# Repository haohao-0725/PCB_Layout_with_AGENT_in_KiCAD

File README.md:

# PCB Layout with an AI Agent in KiCad (`kicad-clean-pcb`)

[繁體中文說明](README.zh-TW.md)

**An AI agent takes your working prototype to a tidy, fab-ready KiCad board: you approve every
decision, the placement is checked on paper before routing, and tidiness is measured, not
eyeballed.**

See a complete board generated end to end with the bundled tools, from wiring plan to fab zip:
[examples/stepper-carrier-2axis](examples/stepper-carrier-2axis/) (NUCLEO-F446ZE + 2 × TMC2209,
4 layers, ERC/DRC/parity 0, no vias).

An **Agent Skill for Claude Code and OpenAI Codex**. It takes a **KiCad PCB** from a working
prototype to fab-ready **Gerber and drill files**, and keeps you in the loop:

- you choose the design style up front,
- you approve every add-on circuit in a yes/no checklist,
- you confirm the placement on a **1:1 printout before a single track is routed**.

It is **not an autorouter**. It is the workflow, layout rules and checks that make an AI agent
behave like a careful PCB designer, for hand-soldered control boards, motor-driver boards and
module carrier boards.

## Why this exists

It came out of turning a perfboard prototype into a 4-layer carrier board. The prototype had an
MCU dev board, stepper-driver modules, encoder receivers and current-sense modules.

The agent's first attempt used automatic placement and grid routing. It passed DRC, but it had:

- about 10,000 zigzag track segments,
- four copper pours,
- a layout nobody could follow.

The restructured board had about 600 segments and 30 vias, one GND plane, and a third less
board area.

The 1:1 paper check came too late, after routing. It found a USB port blocked by a header row,
a fuse holder whose pitch didn't match the real part, and a terminal block that duplicated one
already on a module. All three meant rerouting.

This skill captures what fixed those problems, so the next board doesn't repeat them:

- **Decide in writing, early.** Preferences and add-on circuits are settled before the
  schematic, in a file both sides can read (`PCB_DECISIONS.md`).
- **Place, print, confirm, then route.** Mechanical mistakes surface on paper, not after
  routing.
- **Route by function group, one group at a time.** Straight lines and 45° corners, a main
  direction per layer, few vias. Run DRC after each group.
- **Nothing unrequested.** No protection, buffers or test points the user didn't approve. And
  no silently skipped protection either.

## What's inside

- **A 7-stage workflow with 4 checkpoints:** requirements and wiring → parts and decisions →
  schematic → placement (1:1 check) → routing → verification and fab files → close-out.
- **Three design presets, plus 17 adjustable axes:** Tidy & readable, Compact / shortest,
  Robust / max electrical. The axes cover stackup, vias, pours, protection policy, current
  target, temperature-rise limit, assembly method, silkscreen, checkpoint cadence and more.
- **`PCB_DECISIONS.md`, a yes/no handshake template.** It has:
  - a scope check (mains, >60 V, Li-ion, high-speed, safety-critical),
  - your preferences,
  - one row per optional protection or add-on circuit,
  - one row per optional technical check,
  - checkpoint sign-offs and a change log.

  A blank row means "not approved".
- **Reference guides:** layout rules per style; circuit policy (add-on classes A–D, current
  ratings, reverse-polarity options, regenerated motor energy); a routing playbook with
  stackup options; verification and order-spec templates; KiCad 10 scripting notes.
- **Board tools (`kcp`)** that read the `.kicad_pcb` file directly, plus four scripts. Both are
  listed under [Tools and scripts](#tools-and-scripts). The tidiness lint turns "is this layout
  readable?" into numbers: segments per mm, zigzag turns, off-angle segments, vias on power
  nets, layer directions, non-GND pours, part-row alignment.

## Is it for you?

**Good fit**

- You have a working prototype (perfboard, breadboard, jumper wires, dev boards and modules) and
  want a real PCB.
- Low and medium-speed boards: microcontroller I/O, motor drivers, sensors, encoders,
  RS-422/RS-485, I²C/SPI/UART.
- You use Claude Code, Codex or another agent that supports Agent Skills, and you want to
  approve the important decisions yourself.

**Not a fit**

- RF, DDR, USB high-speed or other controlled-impedance designs; mains-powered or isolated
  supplies; battery charging; anything above 60 V DC; safety-critical or medical devices. The
  skill's scope check stops and says so.
- "Generate my whole board without asking me anything." This skill asks, on purpose, at four
  checkpoints.

## Requirements and version notes

| | Tested | Notes |
|---|---|---|
| KiCad | **10.0.x** | `kicad-cli` options and Gerber file naming change between versions. The skill checks `--help` and reads Gerber layers from X2 attributes instead of file extensions |
| OS | Windows 10 | macOS and Linux should work, but the paths in the docs are Windows-first and untested elsewhere |
| Python for `kcp` and the board scripts | 3.9+ (stdlib only) | Reads and writes the KiCad files directly; nothing imports `pcbnew` (deprecated, removed in KiCad 11). `kicad-cli` is used for DRC, ERC, netlists, previews and fab output |
| Python for Gerber tools | 3.8+ (stdlib only) | `gerber_readback.py` and `compare_gerbers.py` need no KiCad |
| Agents | Claude Code, Codex | Any agent that reads `SKILL.md` folders (the Agent Skills format) should work |

## Install

**Pick one method.** If you copied the skill folder into `~/.claude/skills/` before and now
install the plugin, delete `~/.claude/skills/kicad-clean-pcb` first: with both installed, the
name `kicad-clean-pcb` resolves to the copied folder and the agent may follow that older copy.
Start a new session after installing or updating, because skills and MCP tools load when a
session starts. To check, ask the agent to run `python <skill>/kcp doctor --markdown` (MCP tool
`check_setup`): it lists every copy of the skill on the machine with its version and says what
to update or remove.

### Claude Code: plugin marketplace (recommended)

In a Claude Code session:

```text
/plugin marketplace add haohao-0725/PCB_Layout_with_AGENT_in_KiCAD
/plugin install kicad-clean-pcb@pcb-layout-with-agent
```

### Claude Code: copy the skill folder

```bash
git clone https://github.com/haohao-0725/PCB_Layout_with_AGENT_in_KiCAD.git
cp -r PCB_Layout_with_AGENT_in_KiCAD/skills/kicad-clean-pcb ~/.claude/skills/
```

For a single project, use `<project>/.claude/skills/` instead.

### Codex

```bash
cp -r PCB_Layout_with_AGENT_in_KiCAD/skills/kicad-clean-pcb ~/.agents/skills/
```

For a single repository, use `<repo>/.agents/skills/`. Older Codex releases read
`~/.codex/skills/`. Restart Codex after installing.

### Updating

Claude Code doesn't update plugins from third-party marketplaces on its own (auto-update is off
for them by default), and a session keeps the version it started with. To update:

```bash
claude plugin marketplace update pcb-layout-with-agent
claude plugin update kicad-clean-pcb@pcb-layout-with-agent
```

Or, in a session: `/plugin`, **Installed** tab, `kicad-clean-pcb`, **Update now**. To have it
update by itself: `/plugin`, **Marketplaces** tab, `pcb-layout-with-agent`, **Enable
auto-update**. Then start a new session. To update a copied folder, `git pull` the clone and copy
the folder again. `kcp doctor` reports any copy that is older than the newest one on the machine.

**Claude desktop app.** The app runs its own copy of Claude Code, which is not on PATH, so a
terminal answers that it can't find `claude`. Ask the agent in a Code session to update the
plugin: `kcp doctor` gives it the full path of the app's copy. Or, on Windows, run it yourself in
PowerShell (the folder name has the app's version in it and changes when the app updates):

```powershell
$claude = (Get-ChildItem "$env:APPDATA\Claude\claude-code\*\*\claude.exe" | Sort-Object LastWriteTime | Select-Object -Last 1).FullName
& $claude plugin marketplace update pcb-layout-with-agent
& $claude plugin update kicad-clean-pcb@pcb-layout-with-agent
```

Then start a new session.

### Windows (PowerShell)

```powershell
Copy-Item -Recurse PCB_Layout_with_AGENT_in_KiCAD\skills\kicad-clean-pcb $HOME\.claude\skills\
```

## Quick start

Just describe the board. For example:

- "Turn my perfboard stepper controller into a PCB. Here are the pin map, BOM and photos."
- "Here's my KiCad schematic. Help me place it and route it so it's readable."
- "Check these Gerbers before I order them."

The agent starts with the scope check and asks you to pick a preset. Then it creates
`PCB_DECISIONS.md` in your project. From there, every checkpoint is a single message listing
everything that needs your answer.

## Design presets

| | T · Tidy & readable | C · Compact / shortest | R · Robust / max electrical |
|---|---|---|---|
| Goal | Read the layout at a glance; easy to hand-solder and modify | Smallest board, shortest connections, lowest cost | Best signal integrity, thermal margin and fault tolerance |
| Routing | Straight + 45°, one direction per layer, ordered lanes | Shortest 45° paths | As T, plus return-path rules |
| 4-layer stackup | Sig / GND / GND / Sig | Sig / GND / Power / Sig | Sig / GND / GND / Sig |
| Add-on circuits | Minimal (prototype is the baseline) | Minimal | Full protection at external interfaces |
| Current target / ΔT limit | 2 × measured / 20 °C | 2 × measured / 20 °C | Worst case / 10 °C |

You can mix and match, e.g. a tidy layout with full protection. All presets keep the 1:1 fit
check, measured footprints, native checks at zero, and a Gerber readback with a layer-order
table.

## The workflow

| Stage | Output | You confirm |
|---|---|---|
| 0. Scope, profile, preferences | `PCB_DECISIONS.md` Part A | ✔ |
| 1. Hardware list, requirements, wiring plan | Project brief | ✔ |
| 2. Parts gaps, add-on decisions | BOM, measured dimensions, yes/no rows answered | ✔ |
| 3. Schematic | ERC clean, netlist checked against the wiring plan | if needed |
| 4. Placement | Previews and a **1:1 fit-check PDF** | ✔ **no routing before this** |
| 5. Routing | Grouped routing, DRC after each group | at the end |
| 6. Verification and fab files | DRC/parity zero, Gerbers + drill + readback, order spec | ✔ |
| 7. Close-out | One rebuild entry point, archived old files, handoff notes | — |

## Tools and scripts

### Board tools: `kcp`

Any Python 3.9+, no KiCad needed except for `drc` and `erc`. Each command prints JSON, or
Markdown tables with `--markdown`. Exit code 1 means the check failed; 2 means the tool could
not run.

| Command | What it does |
|---|---|
| `inspect` | The board as JSON: outline size, layers and stackup, footprints with position, rotation, side, courtyard and pads, nets with netclass and routing stats, tracks, vias and zones. `--drc` adds unconnected items per net |
| `lint` | Tidiness score against a preset (T, C or R), pass / warn / fail per metric. Thresholds live in `kcp/presets/lint.json`; pass your own copy with `--thresholds`. Give it a layer plan (`examples/layer-plans/`) to check each layer's main direction |
| `decisions` | Blank rows in `PCB_DECISIONS.md`, in any language. `--checkpoint CP2` exits 1 while anything CP2 needs is unanswered |
| `drc`, `erc` | kicad-cli DRC / ERC summarised by type, unconnected items per net. DRC also lists every item with the parts involved and its position, named the same in any KiCad UI language. It runs on a temporary copy, so nothing is written next to your board; `--refill --save` has KiCad fill the zones and save the board |
| `place` | `fit-check` (courtyard overlaps, edge distance, silkscreen past the edge, keep-outs), `move`, `row`, `edge` (courtyard and silkscreen flush with the edge; `--entry auto` turns screw terminals, JST PH/XH/EH, barrel jacks and USB parts so the cable goes in from outside). Writes refuse while KiCad has the project open |
| `route` | `path`: pad → bend points → pad, written only if every segment is 0/45/90° and keeps the netclass clearance; otherwise a list of conflicts. `lane`: crossing-free order for a lane. `cleanup`: merge collinear segments |
| `previews`, `tracedrop` | Review PDFs/PNGs (top layer drawn last; a page per outer layer when it has a pour) and the 1:1 fit-check page; voltage drop and temperature rise of a net |
| `fab` | Gerbers + drill, a zip with README.txt and SHA256SUMS.txt, and a readback of the zip against the board (size, copper layers, PTH, NPTH) |
| `new` | Starts a generator project: build, place, route and rebuild scripts for a placeholder board that passes every check, ready to replace with your wiring plan |
| `doctor` | Which copies of the skill are installed (plugin, copied folders) with their versions, which one runs, and what to update |

```bash
python skills/kicad-clean-pcb/kcp inspect board.kicad_pcb --summary --markdown
python skills/kicad-clean-pcb/kcp lint board.kicad_pcb --preset T --layer-plan examples/layer-plans/4L-S1.json --markdown
python skills/kicad-clean-pcb/kcp decisions PCB_DECISIONS.md --checkpoint CP2
python skills/kicad-clean-pcb/kcp drc board.kicad_pcb --refill
python skills/kicad-clean-pcb/kcp fab board.kicad_pcb --out-dir fab --readme order_spec.txt
python skills/kicad-clean-pcb/kcp new my_board --copper 2 && python my_board/rebuild_my_board.py
```

On the board this skill came from, the lint separates the two versions clearly:

| Metric | Autorouted draft | Restructured board |
|---|---:|---:|
| Segments per mm of track | 1.00 | 0.09 |
| Turns per 10 mm (zigzag) | 8.8 | 0.5 |
| Segments not at 0/45/90° | 79 | 0 |
| Vias on power / phase nets | 24 | 0 |
| Pours on nets other than GND | 3 | 0 |
| Worst resistor-row misalignment | 1.35 mm | 0 mm |
| Result (preset T) | fail on 11 metrics | warn (11 short S-bends to review) |

### Scripts

| Script | What it does | Run with |
|---|---|---|
| `export_previews.py` | Routing, assembly and inner-plane previews (PDF + PNG) and a 1:1 fit-check PDF on A4/A3 (same as `kcp previews`) | Python 3.9+ |
| `trace_drop.py` | Voltage drop and IPC-2221 temperature rise along a net's tracks, to each load (same as `kcp tracedrop`) | Python 3.9+ |
| `gerber_readback.py` | Layer functions and copper order from X2 attributes, board outline size, PTH/NPTH hole and slot counts, with optional expected values | Python 3.8+ |
| `compare_gerbers.py` | Geometry diff of two Gerber/drill bundles: lines, arcs, flashes, regions, holes and slots | Python 3.8+ |

```bash
# Windows example; on Windows set PYTHONUTF8=1
python skills/kicad-clean-pcb/scripts/trace_drop.py board.kicad_pcb --net +5V --source J1.1 --load U3.8=0.15 --load J5.1=0.2
python skills/kicad-clean-pcb/scripts/gerber_readback.py fab.zip --expect-size 100x80 --expect-copper 4 --markdown
python skills/kicad-clean-pcb/scripts/compare_gerbers.py old.zip new.zip
```

Run the unit tests (no KiCad needed; one integration test runs only when `kicad-cli` is installed):

```bash
python -m unittest discover -s tests -v
```

## MCP server and live mode

The same tools are available as an MCP server, one tool per `kcp` command (18 tools: setup check,
inspect, lint, decisions, DRC, ERC, place, route, previews, trace drop, fab output, Gerber readback
and compare; the table is in `SKILL.md`). Every result carries `kcp_version`, the version of the
server that answered. Read-only tools are marked as such; tools that write say so.
The MCP tools check, place and route a board and write the fab files. Creating a schematic and a
board from nothing needs an agent that can run Python (`kcp new`).

- **Claude Code:** installing the plugin registers the server (`mcpServers` in `.claude-plugin/plugin.json`
  runs `python <plugin>/skills/kicad-clean-pcb/kcp mcp`). It needs `python` on your PATH (3.9+);
  where only `python3` exists (common on macOS and Linux), make `python` available first (for
  example `python-is-python3` on Debian/Ubuntu), or the server does not start.
- **Codex** (`~/.codex/config.toml`):

  ```toml
  [mcp_servers.kicad-clean-pcb]
  command = "python"
  args = ["/path/to/skills/kicad-clean-pcb/kcp", "mcp"]
  ```
- **Other agents:** any MCP client that starts a stdio server:
  `{"command": "python", "args": ["/path/to/skills/kicad-clean-pcb/kcp", "mcp"]}`.

With the official SDK installed (`pip install mcp`, 1.x or 2.x) the server uses it; without it, a
small built-in stdio server with the same tools runs instead, so nothing extra is required.

**Live mode (KiCad IPC API).** Pass `live` instead of a board file to `inspect`, `lint`,
`place fit-check`, `place move` and `route path` (CLI or MCP) to work on the board open in KiCad,
saved or not. Every edit is one KiCad commit named like `kcp: route X_DIR`, so one Ctrl+Z undoes
it, and nothing is written when a check fails. To use it:

1. `pip install kicad-python` (module `kipy`; 0.8 targets KiCad 10.0.6, so update KiCad first).
2. In KiCad, enable the API server: Preferences → Plugins (KiCad 9/10). It is stored as
   `api.enable_server` in `kicad_common.json`.
3. Keep KiCad running with the board open.

KiCad 10's API has no schematic commands and cannot load library footprints, so schematic work,
new footprints and fab output stay on the file backend and `kicad-cli`. Live mode is covered by
tests against a stand-in for `kipy`; it has not yet been run against a live KiCad session in this
repository.

## Saving your defaults

If you always start the same way, keep a filled Part A in a file of your own, **outside** the
installed skill folder (updates overwrite it). Start from
[`examples/defaults/PCB_PART_A_DEFAULTS.md`](examples/defaults/PCB_PART_A_DEFAULTS.md), then
point your agent at it from your global notes (`~/.claude/CLAUDE.md` for Claude Code, `AGENTS.md`
for Codex):

```markdown
## PCB work
For the kicad-clean-pcb skill, my default Part A is in ~/pcb-defaults/PCB_PART_A_DEFAULTS.md.
Copy it into each new PCB_DECISIONS.md and ask me once to confirm it.
```

At stage 0 the agent copies it into the project and asks for one confirmation instead of going
through every axis.

## Repository layout

```text
.claude-plugin/          plugin.json (also registers the kcp MCP server) + marketplace.json
skills/kicad-clean-pcb/
  SKILL.md               workflow, checkpoints, principles
  references/            preferences, layout rules, circuit policy, routing, checks, KiCad scripting, regional ordering
  assets/                PCB_DECISIONS and PROJECT_BRIEF templates
  kcp/                   board tools: inspect, lint, decisions, drc/erc, place, route, previews,
                         tracedrop, MCP server, live IPC backend (Python package, stdlib only)
  scripts/               preview, trace, readback and compare tools
  agents/openai.yaml     Codex UI metadata
examples/                saved-defaults example, layer plans for `kcp lint`
tests/                   unit tests and a hand-written test board
docs/                    README images, release steps (RELEASING.md)
pyproject.toml           packaging for `pip install` (optional; the skill folder works on its own)
```

## Limitations and disclaimer

- **Rules of thumb, not a standard.** The rules come from hand-built, low-to-medium-speed boards.
  Verify critical numbers (current, temperature, clearance) against datasheets, IPC standards
  and your fab's capabilities.
- **CAD-clean is not hardware-verified.** Passing DRC says nothing about waveforms, temperature
  or real-world plugging. Test the real board.
- **Estimates only.** `trace_drop.py` uses the IPC-2221 formula and ignores pours, pads and
  connectors.
- **What the Gerber tools skip.** They don't evaluate aperture-macro bodies or step-and-repeat
  blocks.
- **The agent never orders or pays.** It prepares files and specs; you place the order.
- **No warranty.** Provided as is under the MIT license. You are responsible for the boards you
  build.

## Contributing

Issues and pull requests are welcome. These help most:

- reports from other KiCad versions and operating systems,
- layout rules for board types not covered here,
- regional ordering notes,
- a port of the board scripts to KiCad's IPC API.

Please keep proposed rules generic. No project-specific numbers.

## License

[MIT](LICENSE)

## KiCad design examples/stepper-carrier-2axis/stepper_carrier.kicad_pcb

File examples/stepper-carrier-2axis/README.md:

# 範例：2 軸步進馬達載板（NUCLEO-F446ZE ＋ 2 × TMC2209）

`kicad-clean-pcb` skill 從頭走完 Stage 0–6 的完整範例：接線規劃 → 原理圖 → 擺放 → 走線 → 檢查 → 製造檔。
所有 KiCad 檔都由腳本產生，**全程沒有用到 pcbnew（SWIG）**，只用 skill 內的 `kcp` 工具和 `kicad-cli`。

## 狀態

| 項目 | 結果 | 類型 |
|---|---|---|
| ERC | 0 錯誤、0 警告 | CAD 已檢查 |
| KiCad netlist 對照接線規劃 | 24 個元件、每支腳都一致 | CAD 已檢查 |
| DRC／未連線／schematic parity | 0／0／0 | CAD 已檢查 |
| via | 0 個（換層都在 THT 焊盤上） | CAD 已檢查 |
| 鋪銅 | 只有 In1.Cu、In2.Cu 兩層 GND | CAD 已檢查 |
| 整齊度 lint（預設 T、4L-S1 layer plan） | 全部 pass：每 mm 0.10 段、每 10 mm 0.41 個轉折、0 條斜角線段 | CAD 已檢查 |
| 壓降／溫升 | VM 最遠 64 mV、+5V 33 mV、最熱一段 ΔT 4.7 °C | 估算（IPC-2221，只算走線） |
| 製造檔回讀 | 126 × 146 mm、4 層、222 PTH、4 NPTH，與板子一致 | CAD 已檢查 |
| 1:1 實物比對（CP4） | 位置都正確（使用者，2026-10-30） | 實物比對 |
| LM2596 模組焊盤位置 | 1:1 列印比對位置正確；封裝尺寸原本是典型值 | 實物比對 |
| 下單 | 不下單：這塊板只用來示範工具 | — |

整齊度報告：[reports/lint.md](reports/lint.md)。決策紀錄：[PCB_DECISIONS.md](PCB_DECISIONS.md)。
專案簡報：[PROJECT_BRIEF.md](PROJECT_BRIEF.md)。下單規格：[ORDER_SPEC.md](ORDER_SPEC.md)。
實板驗收與量測紀錄（下單、組裝後填寫）：[BRINGUP.md](BRINGUP.md)。

## 板子內容

- **電源：** 12–24 V 端子 J1 → 3 A 慢熔 F1 → 串聯蕭特基 D1（反接保護）→ VM。
  VM 經 B.Cu 1.5 mm 主幹送到兩顆驅動器（各有 470 µF ＋ 100 nF）與 LM2596 降壓模組。
- **5 V：** LM2596 模組輸出接 Nucleo 的 E5V（CN11-6）。
- **驅動器：** 兩顆 MKS TMC2209 V2.0，獨立模式（MS1＝MS2＝GND 為 1/8 微步，PDN_UART 接 GND），
  EN 有 10 kΩ 上拉，MCU 拉低才致能。VIO 接 Nucleo 的 3.3 V。
- **限位：** 兩路常開開關輸入：1 kΩ 串聯 ＋ 10 nF ＋ 10 kΩ 上拉到 3.3 V。
- **版面：** 驅動器與電源在左、Nucleo 在右；所有電線從左緣進板；兩個軸用同一套模板。

## 檔案

| 檔案 | 用途 | 改什麼要改這裡 |
|---|---|---|
| `build_stepper_carrier.py` | 接線規劃（零件、每支腳的 net）、自建封裝（實測尺寸）、netclass 與設計規則 | 電路、元件值、封裝、線寬 |
| `place_stepper_carrier.py` | 板框、GND 平面、每個零件的位置、禁區、絲印 | 位置、方向、板子尺寸 |
| `route_stepper_carrier.py` | 每群一個函式：power、phases、mcu、limits | 走線 |
| `rebuild_stepper_carrier.py` | 唯一入口，從規劃一路做到製造包 | — |
| `stepper_carrier.kicad_*`、`*.kicad_sym`、`*.pretty`、`bom.csv`、`design.json` | 產生物，**不要在 KiCad 直接改** | 改上面的腳本後重建 |
| `reports/` | ERC、netlist 比對、fit check、DRC、lint、壓降、回讀 | — |
| `review/` | 走線、裝件、內層預覽（PNG＋PDF），1:1 試合 PDF | — |
| `fab/` | Gerber、鑽孔與製造壓縮包（含 README.txt 與 SHA256SUMS.txt） | — |

## 重建

先關閉 KiCad（資料夾裡有 `~*.lck` 時腳本會拒絕執行），再用任何 Python 3.9 以上執行：

```bash
python examples/stepper-carrier-2axis/rebuild_stepper_carrier.py
```

需要 KiCad 10 的 `kicad-cli`；要輸出 PNG 預覽還需要 Poppler 的 `pdftoppm`。每一步印一行 `[OK]`／`[FAIL]`，
失敗就停。完整重建約 15 秒。

## 組裝與上電

1. 先焊矮的零件（電阻、陶瓷電容、二極體），再焊排母、端子台、保險絲座、電解電容。
   D1 直立，陰極（色環）在焊盤 1（方形，VM 那側）。
2. **還沒插 Nucleo 和驅動器之前**：接上 12–24 V，把 LM2596 模組調到 5.0 V。
3. 斷電，把 Nucleo 的電源跳線設在 E5V（見 UM1974），插上 Nucleo。
   **不要把載板的 +5V 接到 CN11-18（Nucleo 的 5 V 輸出）。**
4. 斷電，依絲印方向插上驅動器（EN／VM 那一端朝下），先把 VREF 旋鈕調低。
5. 上電後才連 ST-LINK USB。插拔模組一律先斷電。

## 這個範例刻意沒做的事

- 沒有 TVS、ESD、測試點、電源 LED（精簡策略，見 PCB_DECISIONS Part B）。
- 沒有下單。下單前要先做 CP4 的 1:1 實物比對，並量好 LM2596 模組。

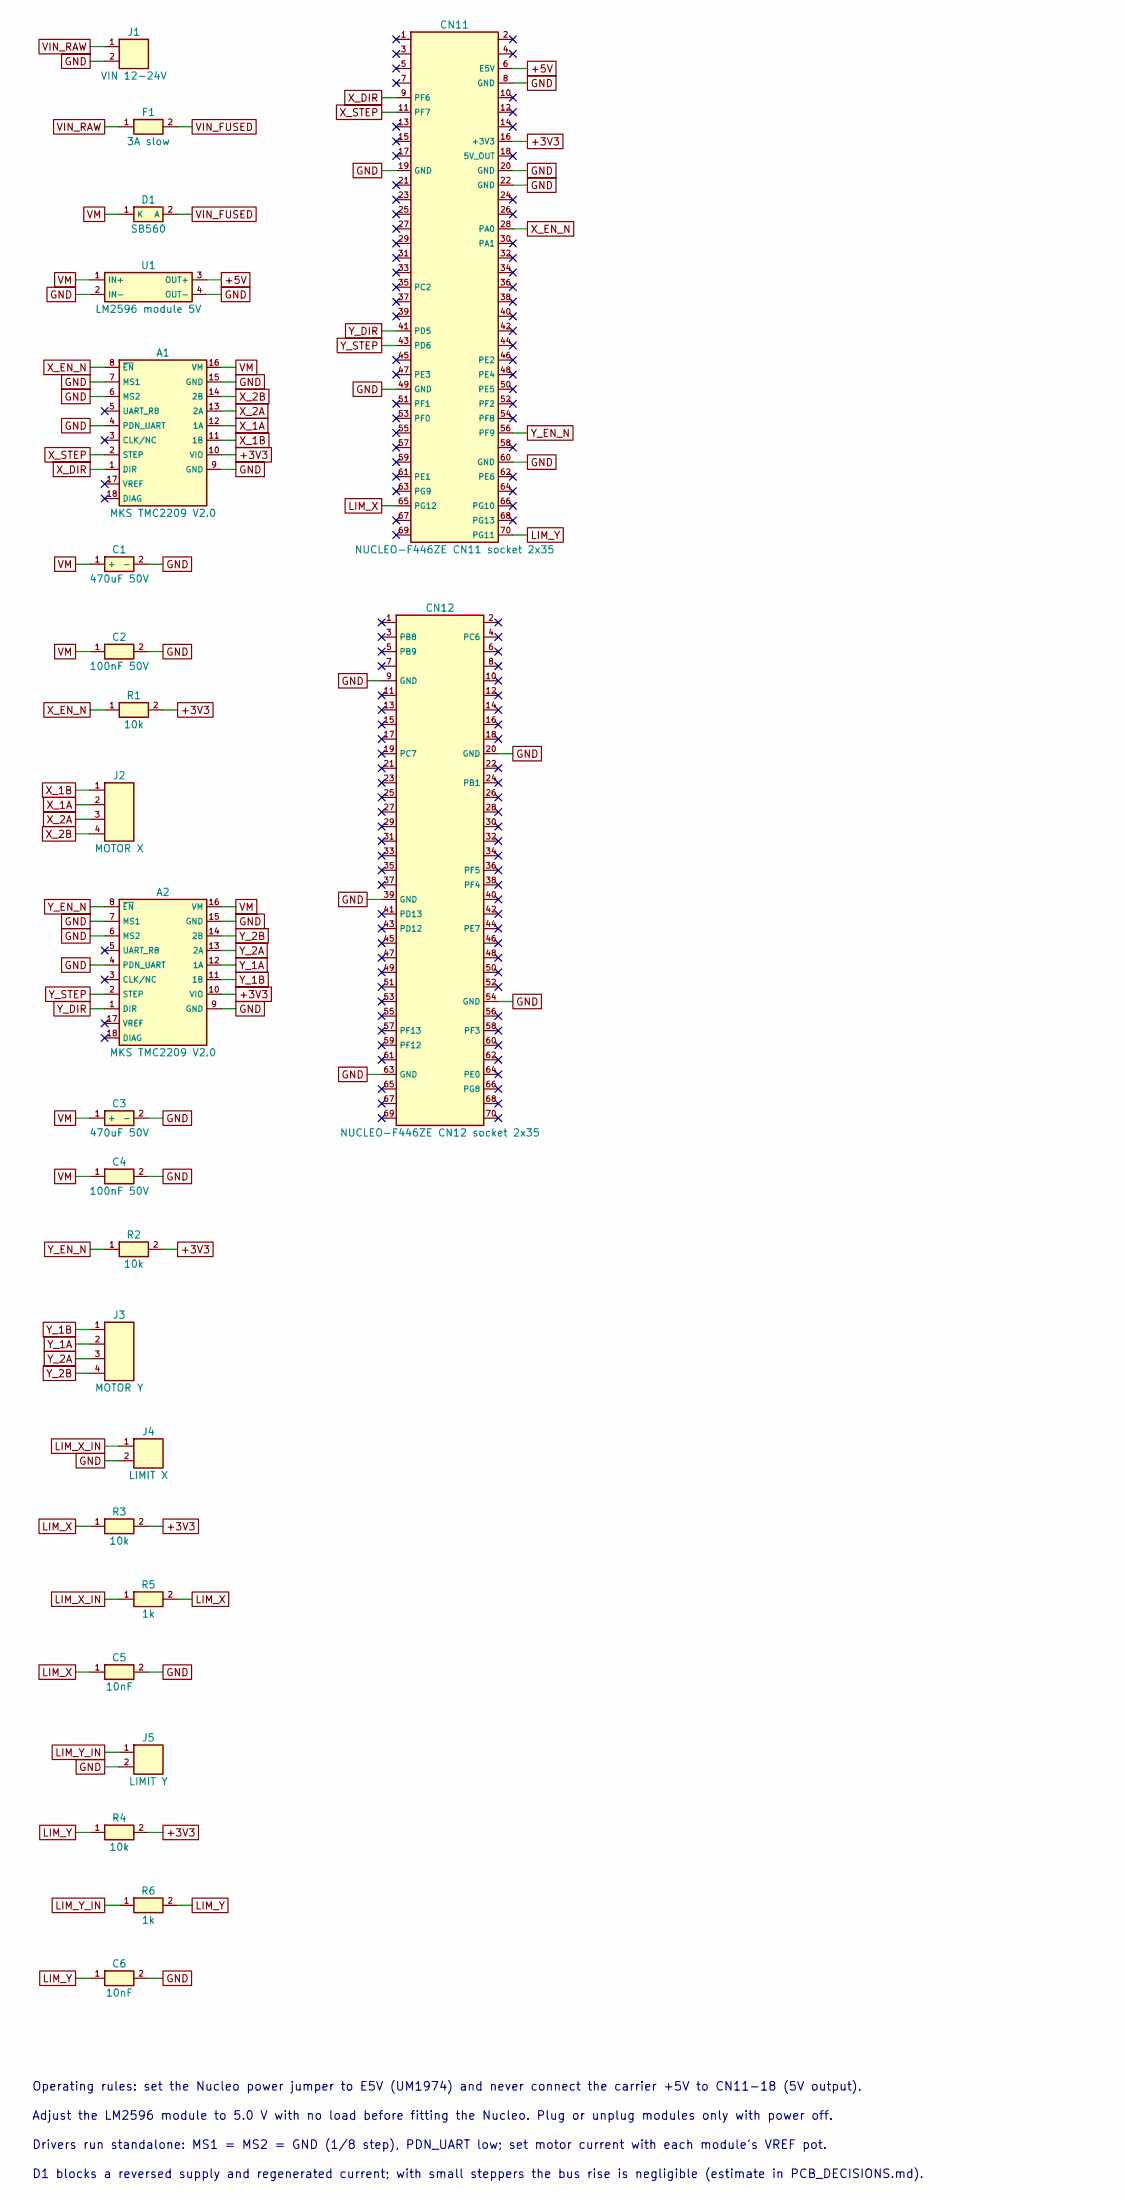
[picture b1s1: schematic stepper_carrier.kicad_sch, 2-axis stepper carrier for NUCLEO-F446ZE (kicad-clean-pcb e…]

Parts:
A1, A2: MKS TMC2209 V2.0; MKS_TMC2209_V2_Sockets_18P
C1, C3: 470uF 50V; CP_Radial_D10.0mm_P5.00mm
C2, C4: 100nF 50V; C_Disc_D5.0mm_W2.5mm_P5.00mm
C5, C6: 10nF; C_Disc_D5.0mm_W2.5mm_P5.00mm
CN11: NUCLEO-F446ZE CN11 socket 2x35; Morpho_2x35_P2.54mm_TopView
CN12: NUCLEO-F446ZE CN12 socket 2x35; Morpho_2x35_P2.54mm_TopView
D1: SB560; D_DO-201AD_P5.08mm_Vertical_AnodeUp
F1: 3A slow; Fuseholder_5x20mm_P23.25mm
J1: VIN 12-24V; Terminal_5.08mm_2P
J2: MOTOR X; Terminal_5.08mm_4P
J3: MOTOR Y; Terminal_5.08mm_4P
J4: LIMIT X; PinHeader_1x02_P2.54mm_Vertical
J5: LIMIT Y; PinHeader_1x02_P2.54mm_Vertical
R1, R2, R3, R4: 10k; R_Axial_DIN0207_L6.3mm_D2.5mm_P2.54mm_Vertical
R5, R6: 1k; R_Axial_DIN0207_L6.3mm_D2.5mm_P2.54mm_Vertical
U1: LM2596 module 5V; LM2596_Module_43x21mm

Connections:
+3V3: A1.10 (VIO), A2.10 (VIO), CN11.16 (+3V3), R1.2, R2.2, R3.2, R4.2
+5V: CN11.6 (E5V), U1.3 (OUT+)
GND: A1.4 (PDN_UART), A1.6 (MS2), A1.7 (MS1), A1.9 (GND), A1.15 (GND), A2.4 (PDN_UART), A2.6 (MS2), A2.7 (MS1), A2.9 (GND), A2.15 (GND), C1.2 (-), C2.2, C3.2 (-), C4.2, C5.2, C6.2, CN11.8 (GND), CN11.19 (GND), CN11.20 (GND), CN11.22 (GND), CN11.49 (GND), CN11.60 (GND), CN12.9 (GND), CN12.20 (GND), CN12.39 (GND), CN12.54 (GND), CN12.63 (GND), J1.2, J4.2, J5.2, U1.2 (IN-), U1.4 (OUT-)
LIM_X: C5.1, CN11.65 (PG12), R3.1, R5.2
LIM_X_IN: J4.1, R5.1
LIM_Y: C6.1, CN11.70 (PG11), R4.1, R6.2
LIM_Y_IN: J5.1, R6.1
VIN_FUSED: D1.2 (A), F1.2
VIN_RAW: F1.1, J1.1
VM: A1.16 (VM), A2.16 (VM), C1.1 (+), C2.1, C3.1 (+), C4.1, D1.1 (K), U1.1 (IN+)
X_1A: A1.12 (1A), J2.2
X_1B: A1.11 (1B), J2.1
X_2A: A1.13 (2A), J2.3
X_2B: A1.14 (2B), J2.4
X_DIR: A1.1 (DIR), CN11.9 (PF6)
X_EN_N: A1.8 (~EN), CN11.28 (PA0), R1.1
X_STEP: A1.2 (STEP), CN11.11 (PF7)
Y_1A: A2.12 (1A), J3.2
Y_1B: A2.11 (1B), J3.1
Y_2A: A2.13 (2A), J3.3
Y_2B: A2.14 (2B), J3.4
Y_DIR: A2.1 (DIR), CN11.41 (PD5)
Y_EN_N: A2.8 (~EN), CN11.56 (PF9), R2.1
Y_STEP: A2.2 (STEP), CN11.43 (PD6)

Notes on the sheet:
Operating rules: set the Nucleo power jumper to E5V (UM1974) and never connect the carrier +5V to CN11-18 (5V output).
Adjust the LM2596 module to 5.0 V with no load before fitting the Nucleo. Plug or unplug modules only with power off.
Drivers run standalone: MS1 = MS2 = GND (1/8 step), PDN_UART low; set motor current with each module's VREF pot.
D1 blocks a reversed supply and regenerated current; with small steppers the bus rise is negligible (estimate in PCB_DECISIONS.md).

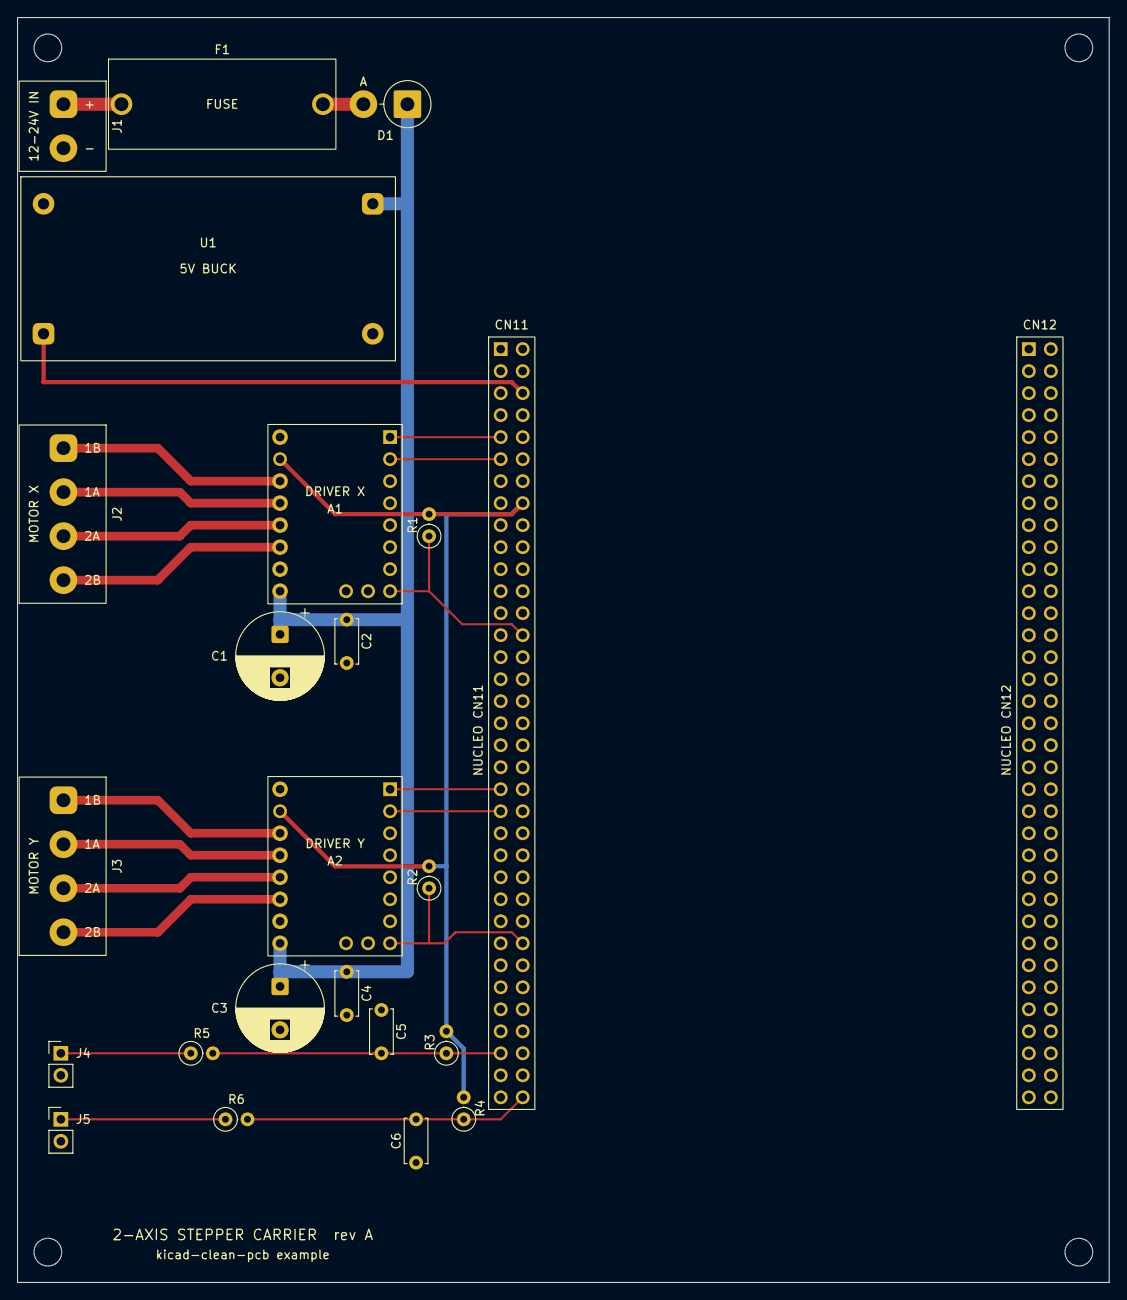
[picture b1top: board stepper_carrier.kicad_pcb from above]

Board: 4 copper layers, 126.0 x 146.0 mm, 28 parts (0 on the bottom side), 24 nets.

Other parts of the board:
H1, H2, H3, H4: MountingHole_3.2mm_M3

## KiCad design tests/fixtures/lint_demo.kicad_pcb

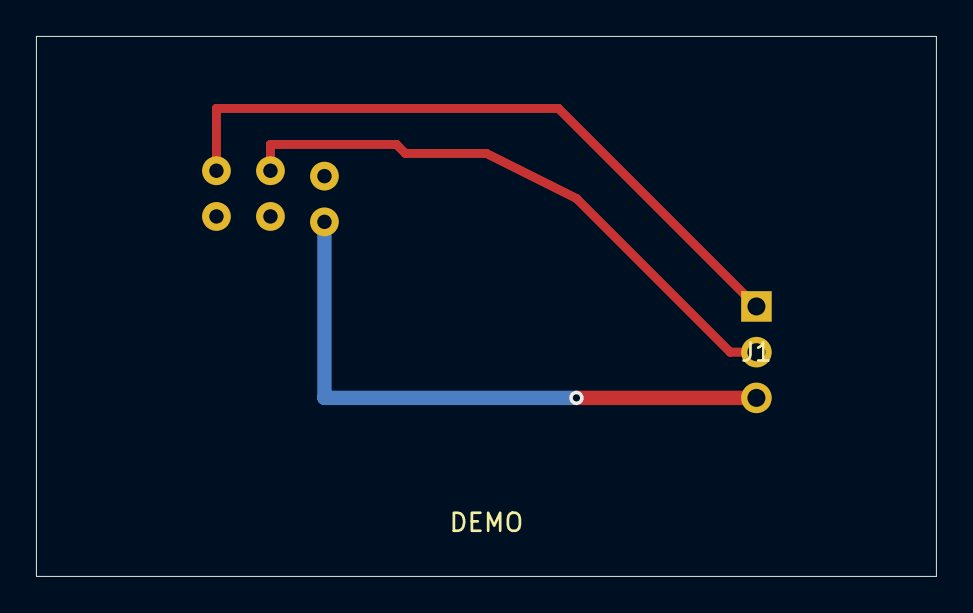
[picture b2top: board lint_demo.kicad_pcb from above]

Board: 4 copper layers, 50.0 x 30.0 mm, 4 parts (0 on the bottom side), 4 nets.

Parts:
J1: Conn_01x03; Header_1x03_P2.54mm
R1, R2: 10k; R_Vertical_P2.54mm
R3: 1k; R_Vertical_P2.54mm

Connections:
+5V: J1.3, R3.1
GND: R1.1, R2.1, R3.2
SIG_A: J1.1, R1.2
SIG_B: J1.2, R2.2
